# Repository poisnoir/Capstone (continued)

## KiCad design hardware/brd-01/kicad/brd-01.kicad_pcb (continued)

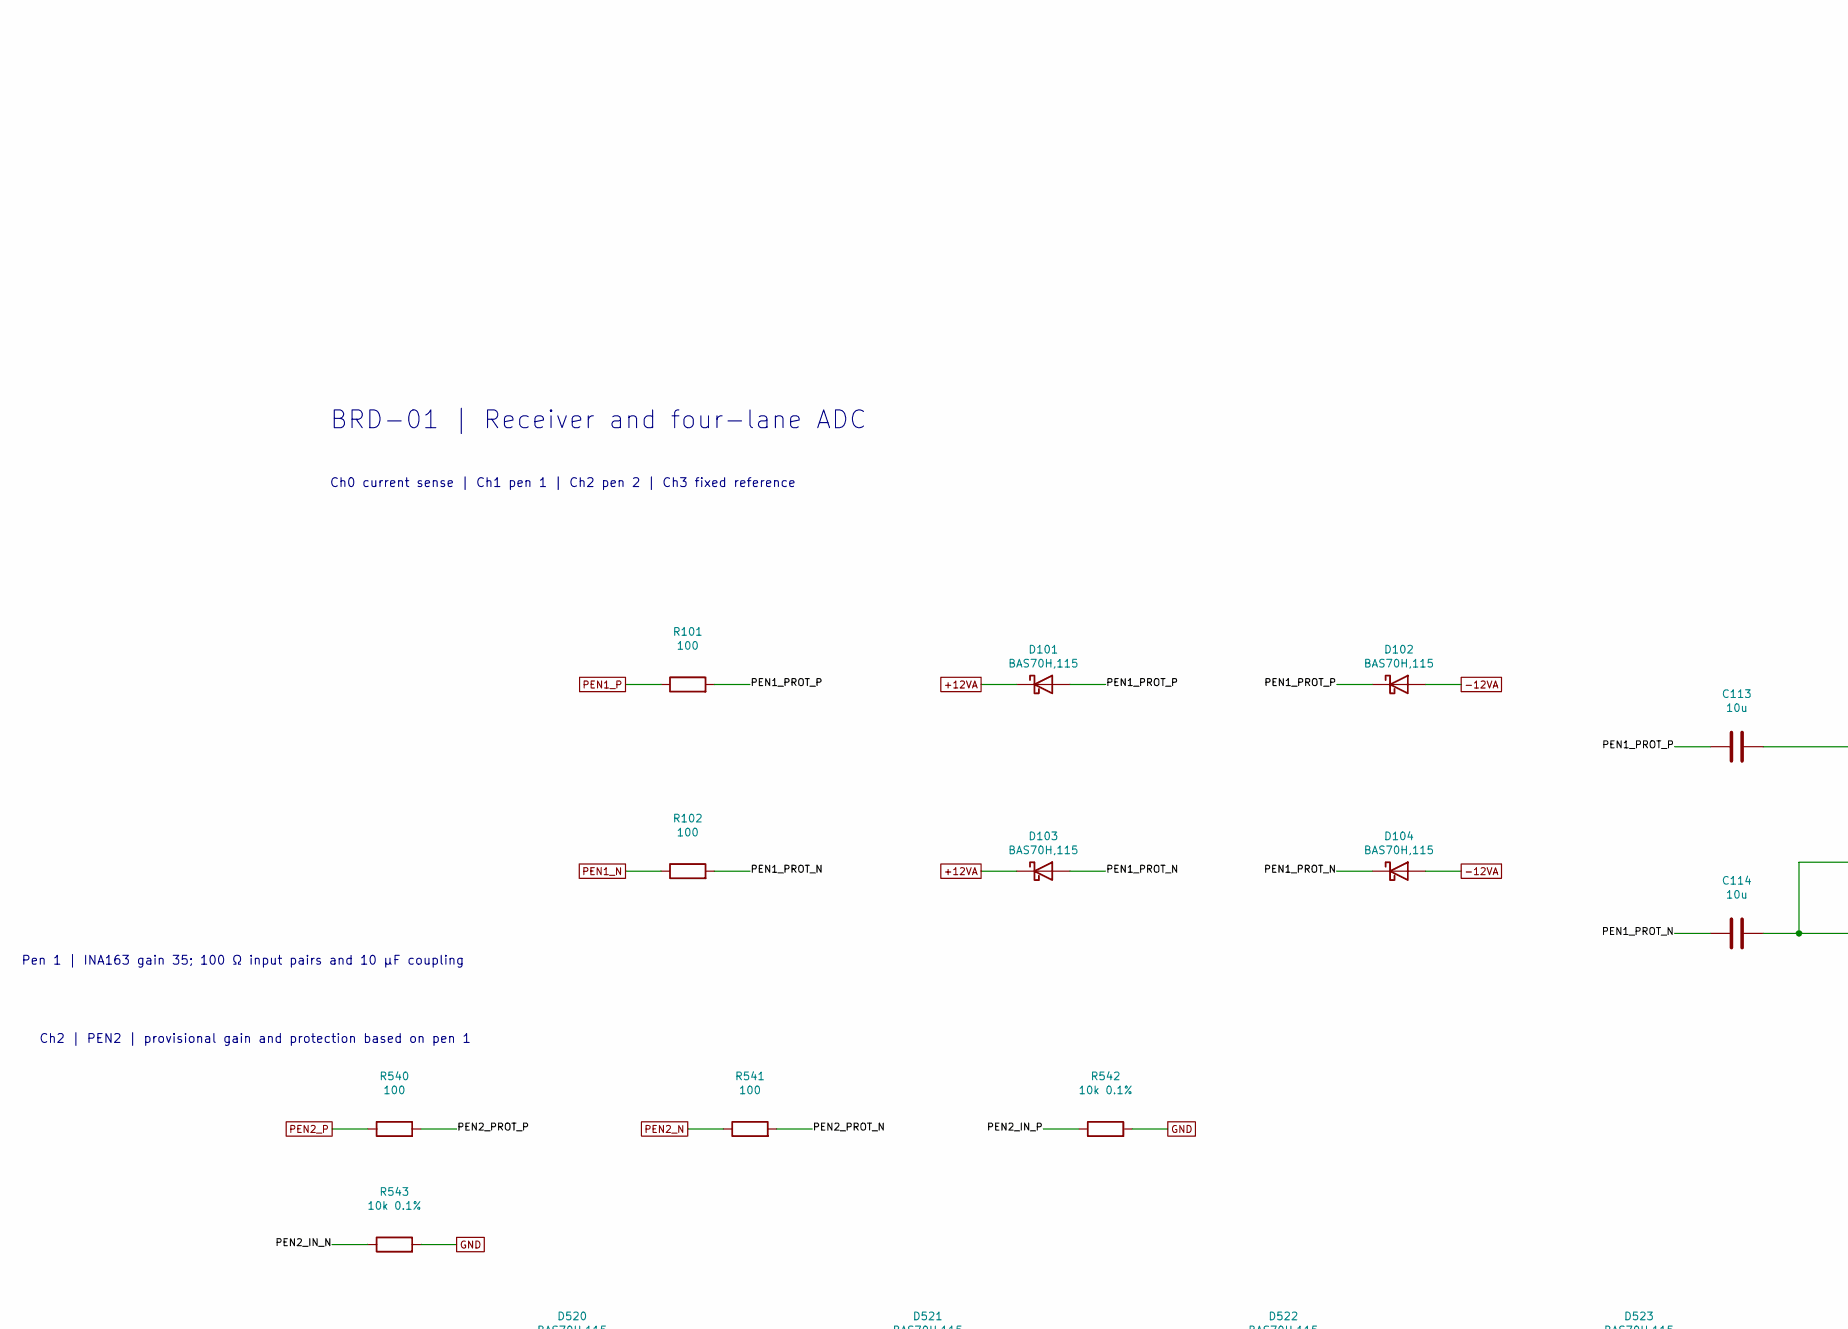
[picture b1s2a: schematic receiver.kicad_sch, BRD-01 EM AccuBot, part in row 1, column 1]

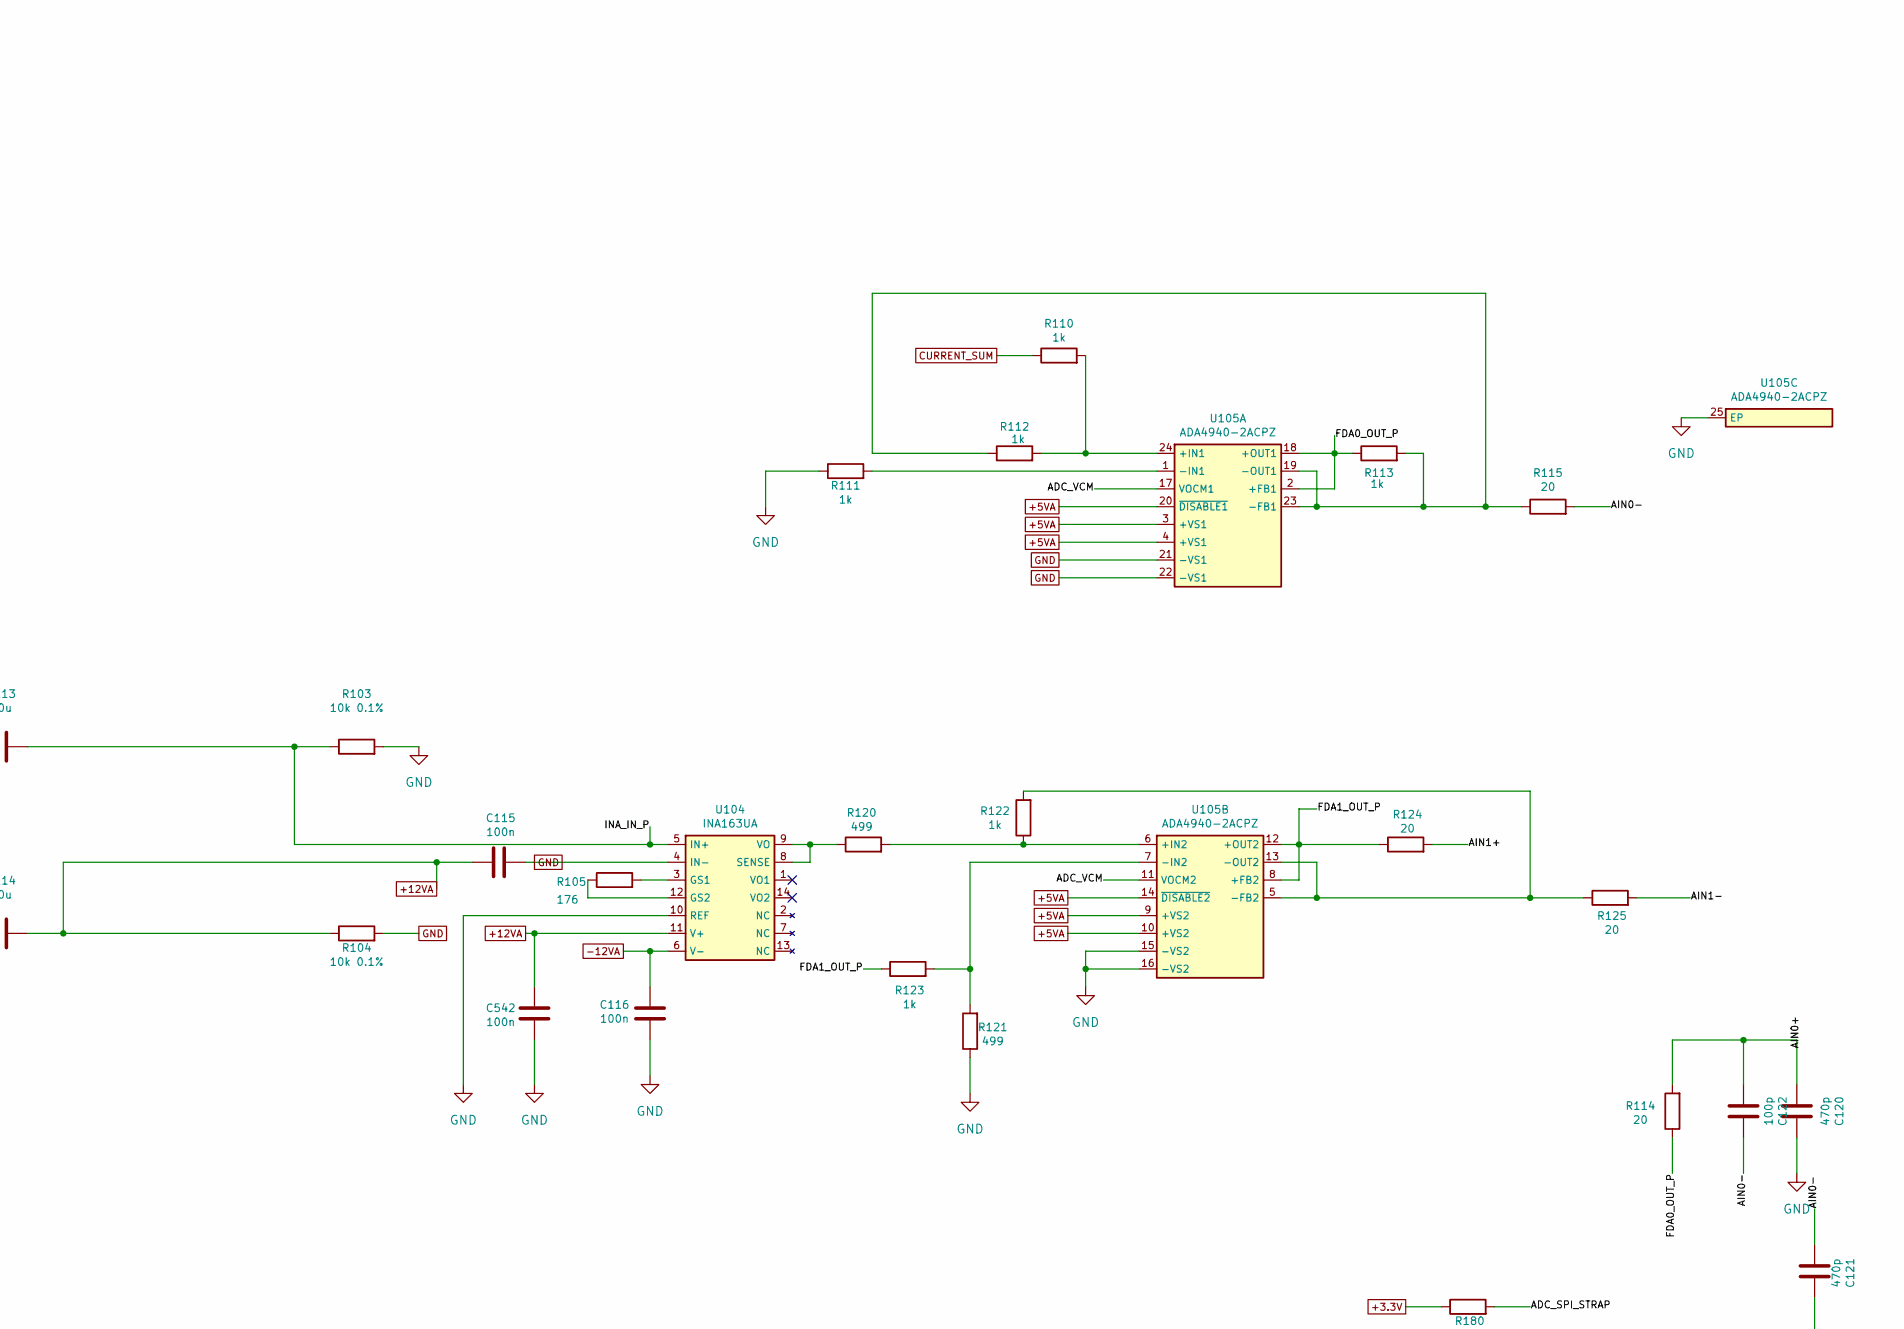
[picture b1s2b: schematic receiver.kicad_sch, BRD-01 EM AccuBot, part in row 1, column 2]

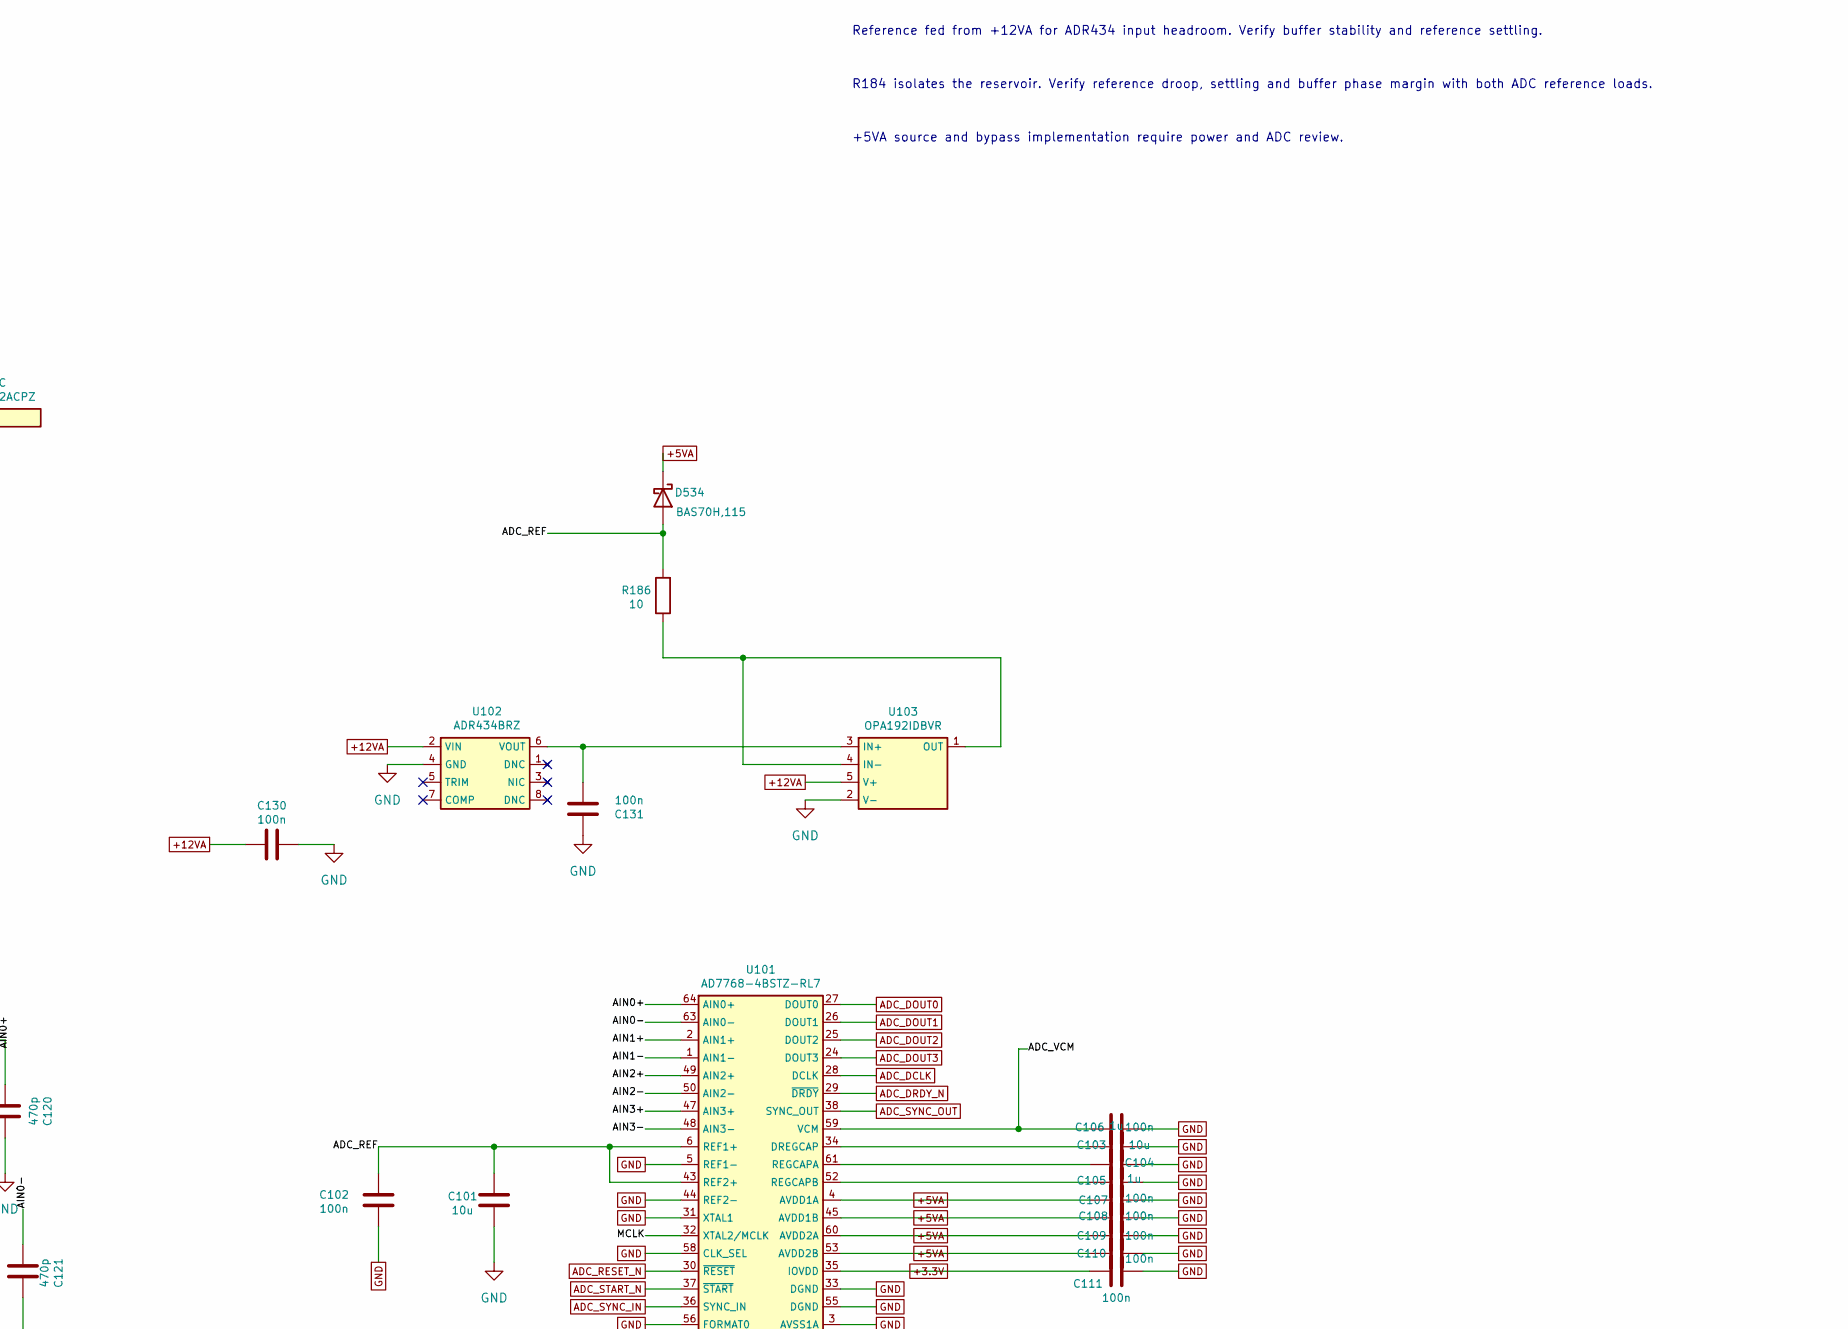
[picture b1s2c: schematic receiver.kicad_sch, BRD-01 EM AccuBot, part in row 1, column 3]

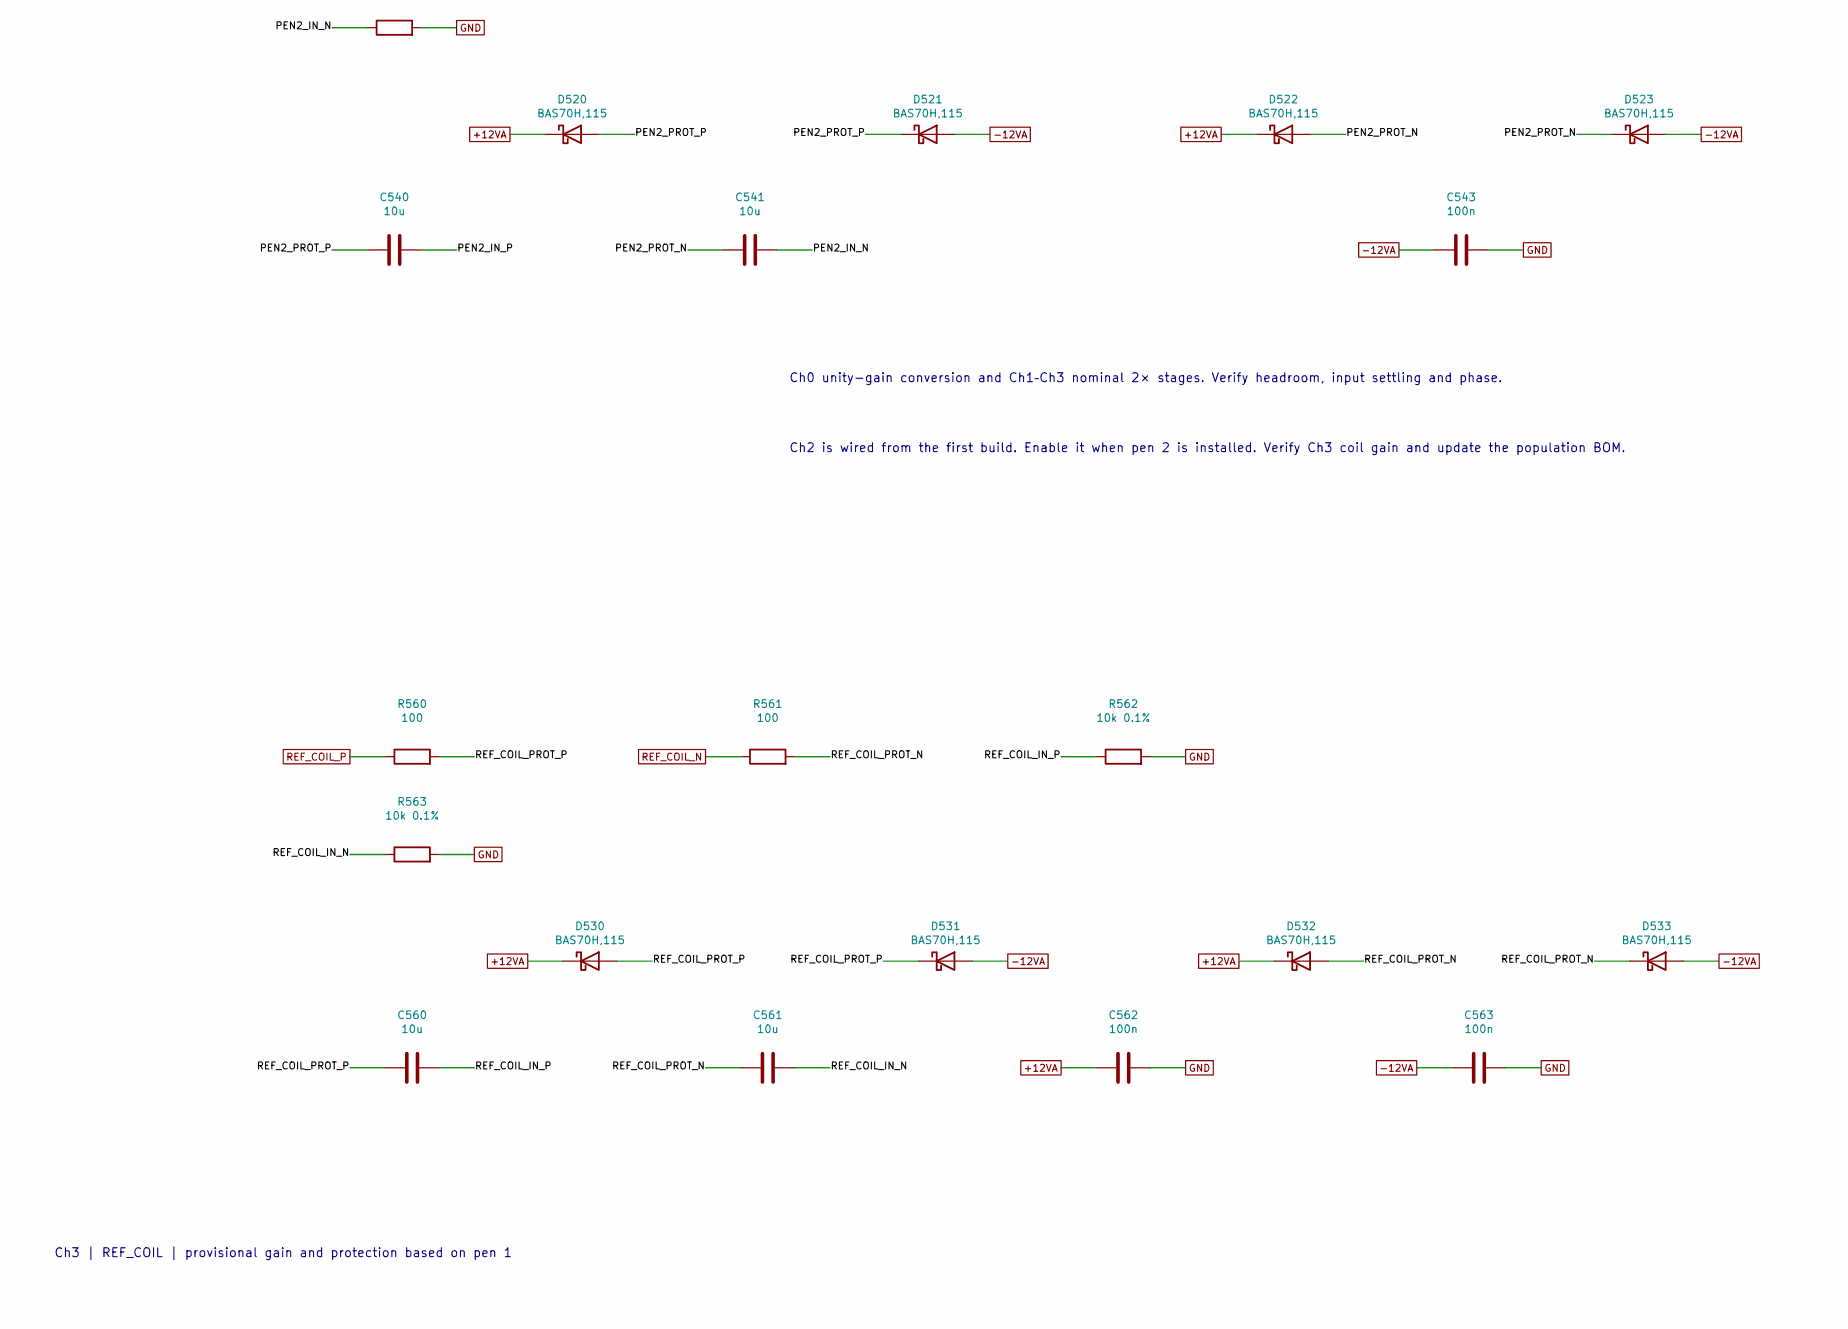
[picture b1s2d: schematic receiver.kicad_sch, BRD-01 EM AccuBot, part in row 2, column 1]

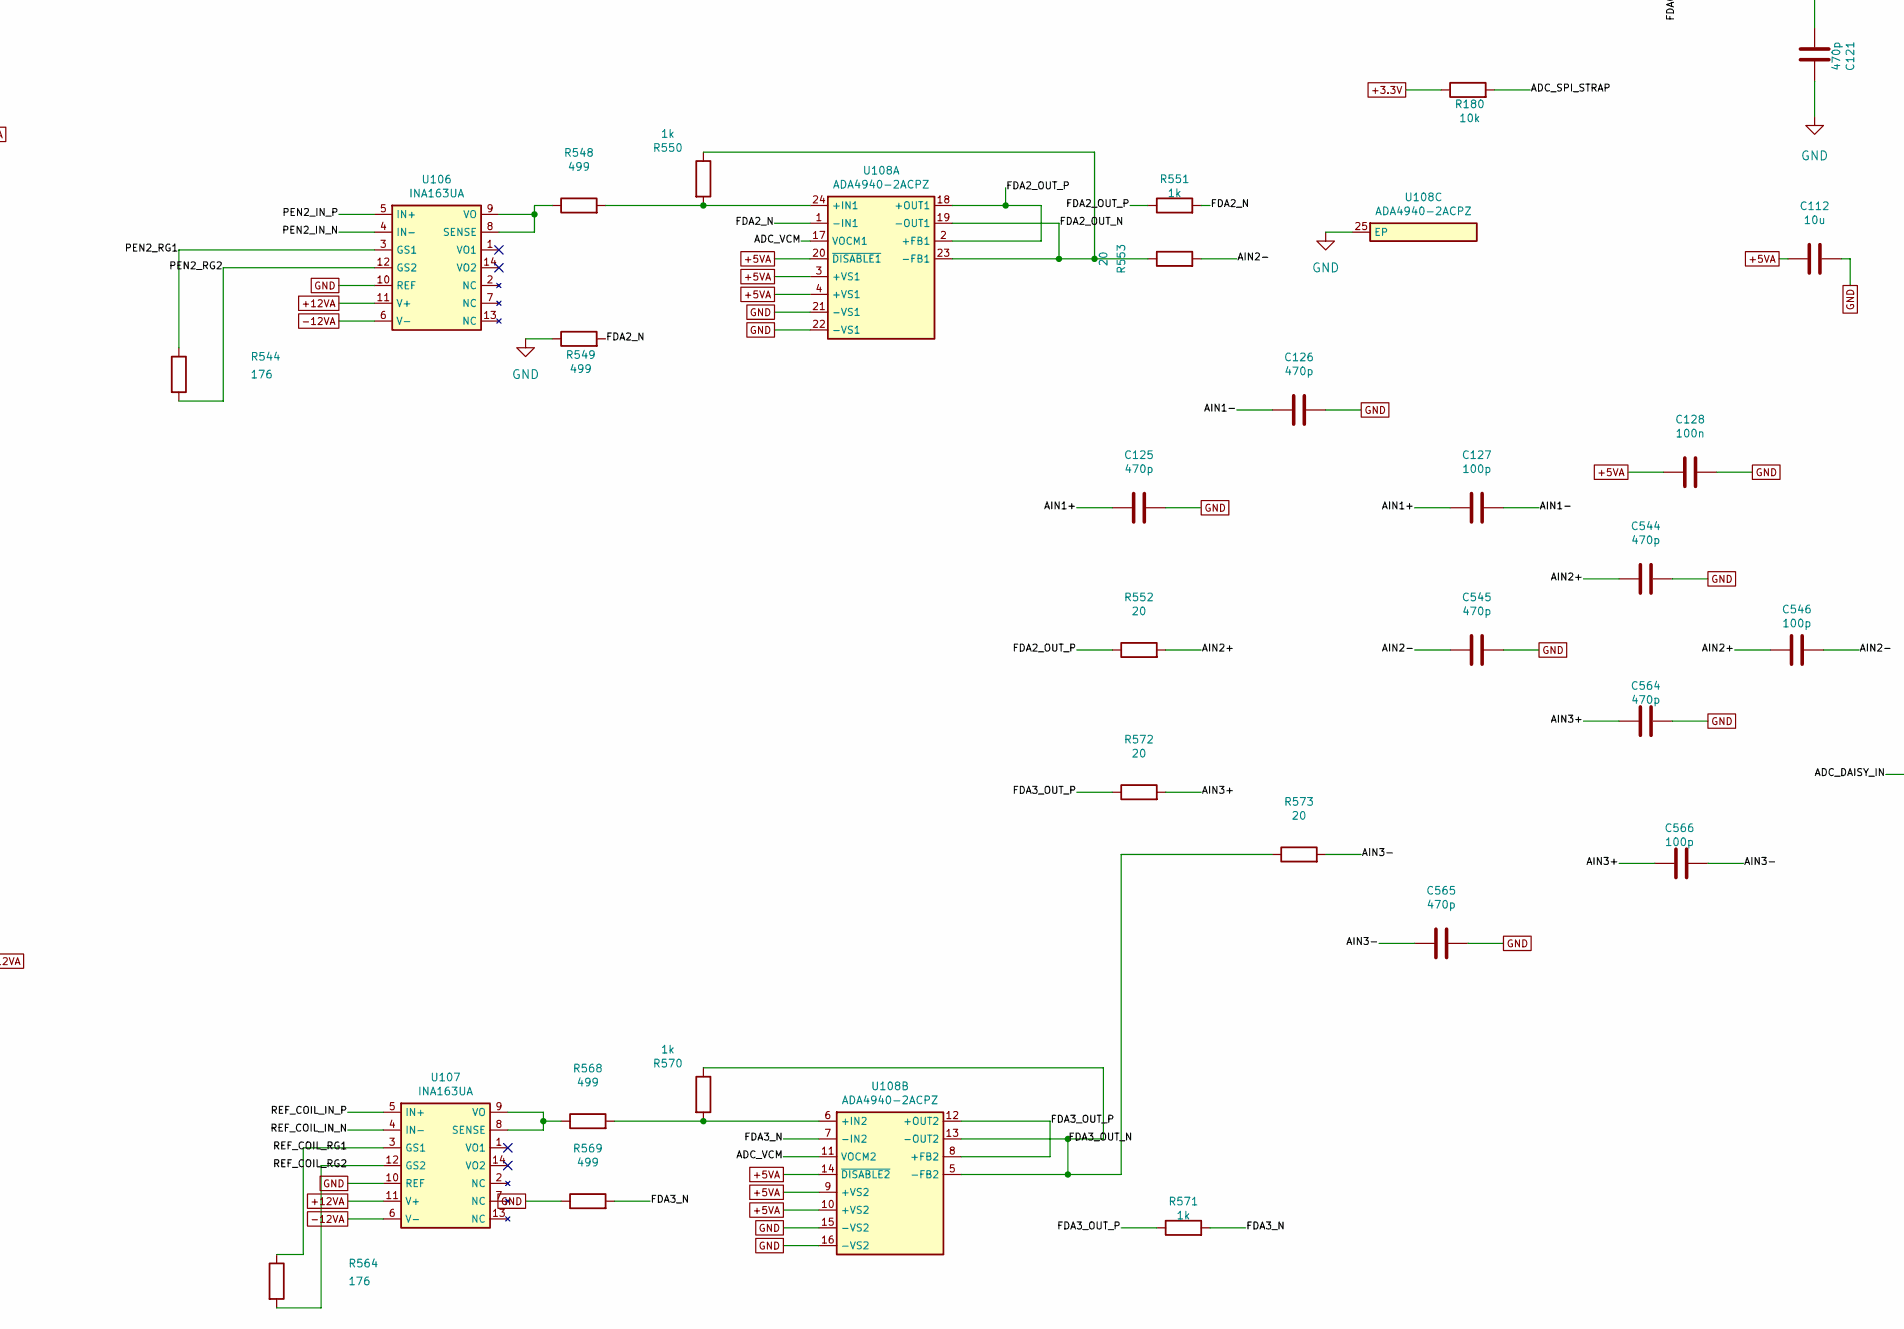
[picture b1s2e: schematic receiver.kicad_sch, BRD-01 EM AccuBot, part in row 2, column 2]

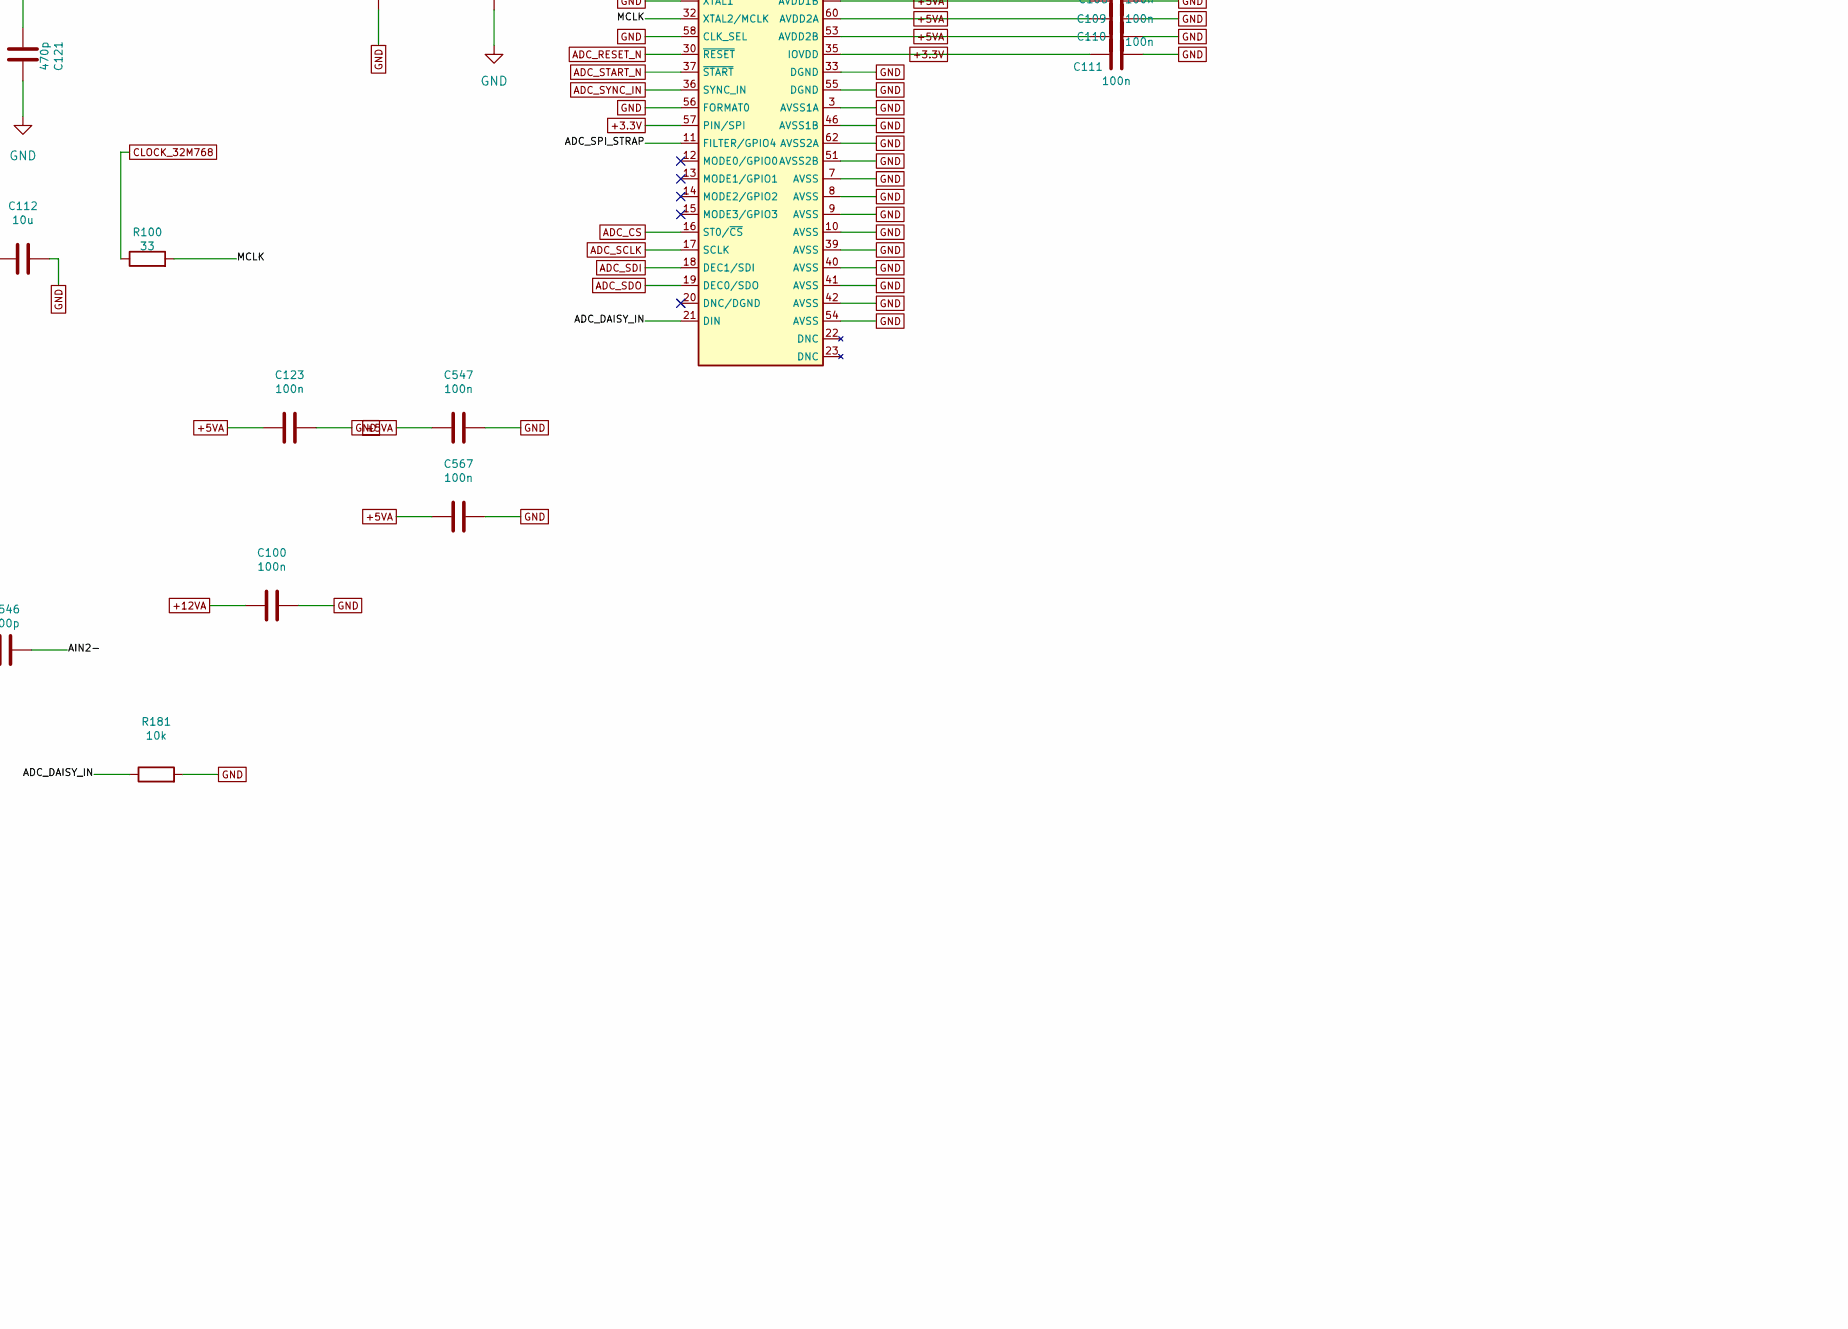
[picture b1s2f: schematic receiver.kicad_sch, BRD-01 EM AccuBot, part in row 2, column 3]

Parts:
C100, C102, C106, C107, C108, C109, C110, C111, C115, C116, C123, C128, C130, C131, C542, C543, C547, C562, C563, C567: 100n; C_0603_1608Metric
C101, C103, C112, C113, C114, C540, C541, C560, C561: 10u; C_1206_3216Metric
C104, C105: 1u; C_0805_2012Metric
C120, C121, C125, C126, C544, C545, C564, C565: 470p; C_0603_1608Metric
C122, C127, C546, C566: 100p; C_0603_1608Metric
D101, D102, D103, D104, D520, D521, D522, D523, D530, D531, D532, D533, D534: BAS70H,115; D_SOD-123F
R100: 33; R_0603_1608Metric
R101, R102, R540, R541, R560, R561: 100; R_0603_1608Metric
R103, R104, R542, R543, R562, R563: 10k 0.1%; R_0603_1608Metric
R105, R544, R564: 176; R_0603_1608Metric
R110, R111, R112, R113, R122, R123, R550, R551, R570, R571: 1k; R_0603_1608Metric
R114, R115, R124, R125, R552, R553, R572, R573: 20; R_0603_1608Metric
R120, R121, R548, R549, R568, R569: 499; R_0603_1608Metric
R180, R181: 10k; R_0603_1608Metric
R186: 10; R_0603_1608Metric
U101: AD7768-4BSTZ-RL7; LQFP-64_10x10mm_P0.5mm
U102: ADR434BRZ; SOIC-8_3.9x4.9mm_P1.27mm
U103: OPA192IDBVR; SOT-23-5
U104, U106, U107: INA163UA; SOIC-14_3.9x8.7mm_P1.27mm
U105, U108: ADA4940-2ACPZ; LFCSP-24-1EP_4x4mm_P0.5mm_EP2.5x2.5mm

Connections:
+3.3V: C111.1, R180.1, U101.35 (IOVDD), U101.57 (PIN/SPI); also elsewhere on the board
+5VA: C107.1, C108.1, C109.1, C110.1, C112.1, C123.1, C128.1, C547.1, C567.1, D534.1 (K), U101.4 (AVDD1A), U101.45 (AVDD1B), U101.53 (AVDD2B), U101.60 (AVDD2A), U105.3 (+VS1), U105.4 (+VS1), U105.9 (+VS2), U105.10 (+VS2), U105.14 (~DISABLE2), U105.20 (~DISABLE1), U108.3 (+VS1), U108.4 (+VS1), U108.9 (+VS2), U108.10 (+VS2), U108.14 (~DISABLE2), U108.20 (~DISABLE1); also elsewhere on the board
+12VA: C100.1, C114.2, C115.1, C130.1, C542.1, C562.1, D101.1 (K), D103.1 (K), D520.1 (K), D522.1 (K), D530.1 (K), D532.1 (K), R104.1, U102.2 (VIN), U103.5 (V+), U104.11 (V+), U106.11 (V+), U107.11 (V+); also elsewhere on the board
-12VA: C116.1, C543.1, C563.1, D102.2 (A), D104.2 (A), D521.2 (A), D523.2 (A), D531.2 (A), D533.2 (A), U104.6 (V-), U106.6 (V-), U107.6 (V-); also elsewhere on the board
/receiver/ADC_DAISY_IN: R181.1, U101.21 (DIN)
/receiver/ADC_REF: C101.1, C102.1, D534.2 (A), R186.2, U101.6 (REF1+), U101.43 (REF2+)
/receiver/ADC_SPI_STRAP: R180.2, U101.11 (FILTER/GPIO4)
/receiver/ADC_VCM: C106.1, U101.59 (VCM), U105.11 (VOCM2), U105.17 (VOCM1), U108.11 (VOCM2), U108.17 (VOCM1)
/receiver/AIN0+: C120.1, C122.1, R114.2, U101.64 (AIN0+)
/receiver/AIN0-: C121.1, C122.2, R115.2, U101.63 (AIN0-)
/receiver/AIN1+: C125.1, C127.1, R124.2, U101.2 (AIN1+)
/receiver/AIN1-: C126.1, C127.2, R125.2, U101.1 (AIN1-)
/receiver/AIN2+: C544.1, C546.1, R552.2, U101.49 (AIN2+)
/receiver/AIN2-: C545.1, C546.2, R553.2, U101.50 (AIN2-)
/receiver/AIN3+: C564.1, C566.1, R572.2, U101.47 (AIN3+)
/receiver/AIN3-: C565.1, C566.2, R573.2, U101.48 (AIN3-)
/receiver/FDA0_OUT_P: R113.1, R114.1, U105.2 (+FB1), U105.18 (+OUT1)
/receiver/FDA1_OUT_P: R123.1, R124.1, U105.8 (+FB2), U105.12 (+OUT2)
/receiver/FDA2_N: R549.2, R551.2, U108.1 (-IN1)
/receiver/FDA2_OUT_N: R550.1, R553.1, U108.19 (-OUT1), U108.23 (-FB1)
/receiver/FDA2_OUT_P: R551.1, R552.1, U108.2 (+FB1), U108.18 (+OUT1)
/receiver/FDA3_N: R569.2, R571.2, U108.7 (-IN2)
/receiver/FDA3_OUT_N: R570.1, R573.1, U108.5 (-FB2), U108.13 (-OUT2)
/receiver/FDA3_OUT_P: R571.1, R572.1, U108.8 (+FB2), U108.12 (+OUT2)
/receiver/INA_IN_P: C113.2, R103.1, U104.5 (IN+)
/receiver/MCLK: R100.2, U101.32 (XTAL2/MCLK)
/receiver/PEN1_PROT_N: C114.1, D103.2 (A), D104.1 (K), R102.2
/receiver/PEN1_PROT_P: C113.1, D101.2 (A), D102.1 (K), R101.2
/receiver/PEN2_IN_N: C541.2, R543.1, U106.4 (IN-)
/receiver/PEN2_IN_P: C540.2, R542.1, U106.5 (IN+)
/receiver/PEN2_PROT_N: C541.1, D522.2 (A), D523.1 (K), R541.2
/receiver/PEN2_PROT_P: C540.1, D520.2 (A), D521.1 (K), R540.2
/receiver/PEN2_RG1: R544.1, U106.3 (GS1)
/receiver/PEN2_RG2: R544.2, U106.12 (GS2)
/receiver/REF_COIL_IN_N: C561.2, R563.1, U107.4 (IN-)
/receiver/REF_COIL_IN_P: C560.2, R562.1, U107.5 (IN+)
/receiver/REF_COIL_PROT_N: C561.1, D532.2 (A), D533.1 (K), R561.2
/receiver/REF_COIL_PROT_P: C560.1, D530.2 (A), D531.1 (K), R560.2
/receiver/REF_COIL_RG1: R564.1, U107.3 (GS1)
/receiver/REF_COIL_RG2: R564.2, U107.12 (GS2)
ADC_CS: U101.16 (ST0/~CS); also elsewhere on the board
ADC_DCLK: U101.28 (DCLK); also elsewhere on the board
ADC_DOUT0: U101.27 (DOUT0); also elsewhere on the board
ADC_DOUT1: U101.26 (DOUT1); also elsewhere on the board
ADC_DOUT2: U101.25 (DOUT2); also elsewhere on the board
ADC_DOUT3: U101.24 (DOUT3); also elsewhere on the board
ADC_DRDY_N: U101.29 (~DRDY); also elsewhere on the board
ADC_RESET_N: U101.30 (~RESET); also elsewhere on the board
ADC_SCLK: U101.17 (SCLK); also elsewhere on the board
ADC_SDI: U101.18 (DEC1/SDI); also elsewhere on the board
ADC_SDO: U101.19 (DEC0/SDO); also elsewhere on the board
ADC_START_N: U101.37 (~START); also elsewhere on the board
ADC_SYNC_IN: U101.36 (SYNC_IN); also elsewhere on the board
ADC_SYNC_OUT: U101.38 (SYNC_OUT); also elsewhere on the board
CLOCK_32M768: R100.1; also elsewhere on the board
CURRENT_SUM: R110.1; also elsewhere on the board
GND: C100.2, C101.2, C102.2, C103.2, C104.2, C105.2, C106.2, C107.2, C108.2, C109.2, C110.2, C111.2, C112.2, C115.2, C116.2, C120.2, C121.2, C123.2, C125.2, C126.2, C128.2, C130.2, C131.2, C542.2, C543.2, C544.2, C545.2, C547.2, C562.2, C563.2, C564.2, C565.2, C567.2, R103.2, R104.2, R111.1, R121.1, R181.2, R542.2, R543.2, R549.1, R562.2, R563.2, R569.1, U101.3 (AVSS1A), U101.5 (REF1-), U101.7 (AVSS), U101.8 (AVSS), U101.9 (AVSS), U101.10 (AVSS), U101.31 (XTAL1), U101.33 (DGND), U101.39 (AVSS), U101.40 (AVSS), U101.41 (AVSS), U101.42 (AVSS), U101.44 (REF2-), U101.46 (AVSS1B), U101.51 (AVSS2B), U101.54 (AVSS), U101.55 (DGND), U101.56 (FORMAT0), U101.58 (CLK_SEL), U101.62 (AVSS2A), U102.4 (GND), U103.2 (V-), U104.4 (IN-), U104.10 (REF), U105.15 (-VS2), U105.16 (-VS2), U105.21 (-VS1), U105.22 (-VS1), U105.25 (EP), U106.10 (REF), U107.10 (REF), U108.15 (-VS2), U108.16 (-VS2), U108.21 (-VS1), U108.22 (-VS1), U108.25 (EP); also elsewhere on the board
unnamed: C103.1, U101.34 (DREGCAP)
unnamed: C104.1, U101.61 (REGCAPA)
unnamed: C105.1, U101.52 (REGCAPB)
unnamed: C131.1, U102.6 (VOUT), U103.3 (IN+)
unnamed: R186.1, U103.1 (OUT), U103.4 (IN-)
unnamed: R105.2, U104.3 (GS1)
unnamed: R105.1, U104.12 (GS2)
unnamed: R120.1, U104.8 (SENSE), U104.9 (VO)
unnamed: R110.2, R112.2, U105.24 (+IN1)
unnamed: R112.1, R113.2, R115.1, U105.19 (-OUT1), U105.23 (-FB1)
unnamed: R111.2, U105.1 (-IN1)
unnamed: R120.2, R122.1, U105.6 (+IN2)
unnamed: R122.2, R125.1, U105.5 (-FB2), U105.13 (-OUT2)
unnamed: R121.2, R123.2, U105.7 (-IN2)
unnamed: R548.1, U106.8 (SENSE), U106.9 (VO)
unnamed: R568.1, U107.8 (SENSE), U107.9 (VO)
unnamed: R548.2, R550.2, U108.24 (+IN1)
unnamed: R568.2, R570.2, U108.6 (+IN2)
PEN1_N: R102.1; also elsewhere on the board
PEN1_P: R101.1; also elsewhere on the board
PEN2_N: R541.1; also elsewhere on the board
PEN2_P: R540.1; also elsewhere on the board
REF_COIL_N: R561.1; also elsewhere on the board
REF_COIL_P: R560.1; also elsewhere on the board

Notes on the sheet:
Ch0 current sense | Ch1 pen 1 | Ch2 pen 2 | Ch3 fixed reference
Pen 1 | INA163 gain 35; 100 Ω input pairs and 10 µF coupling
Reference fed from +12VA for ADR434 input headroom. Verify buffer stability and reference settling.
Ch0 unity-gain conversion and Ch1–Ch3 nominal 2× stages. Verify headroom, input settling and phase.
R184 isolates the reservoir. Verify reference droop, settling and buffer phase margin with both ADC reference loads.
Ch2 | PEN2 | provisional gain and protection based on pen 1
Ch3 | REF_COIL | provisional gain and protection based on pen 1
+5VA source and bypass implementation require power and ADC review.
BRD-01 | Receiver and four-lane ADC
Ch2 is wired from the first build. Enable it when pen 2 is installed. Verify Ch3 coil gain and update the population BOM.
